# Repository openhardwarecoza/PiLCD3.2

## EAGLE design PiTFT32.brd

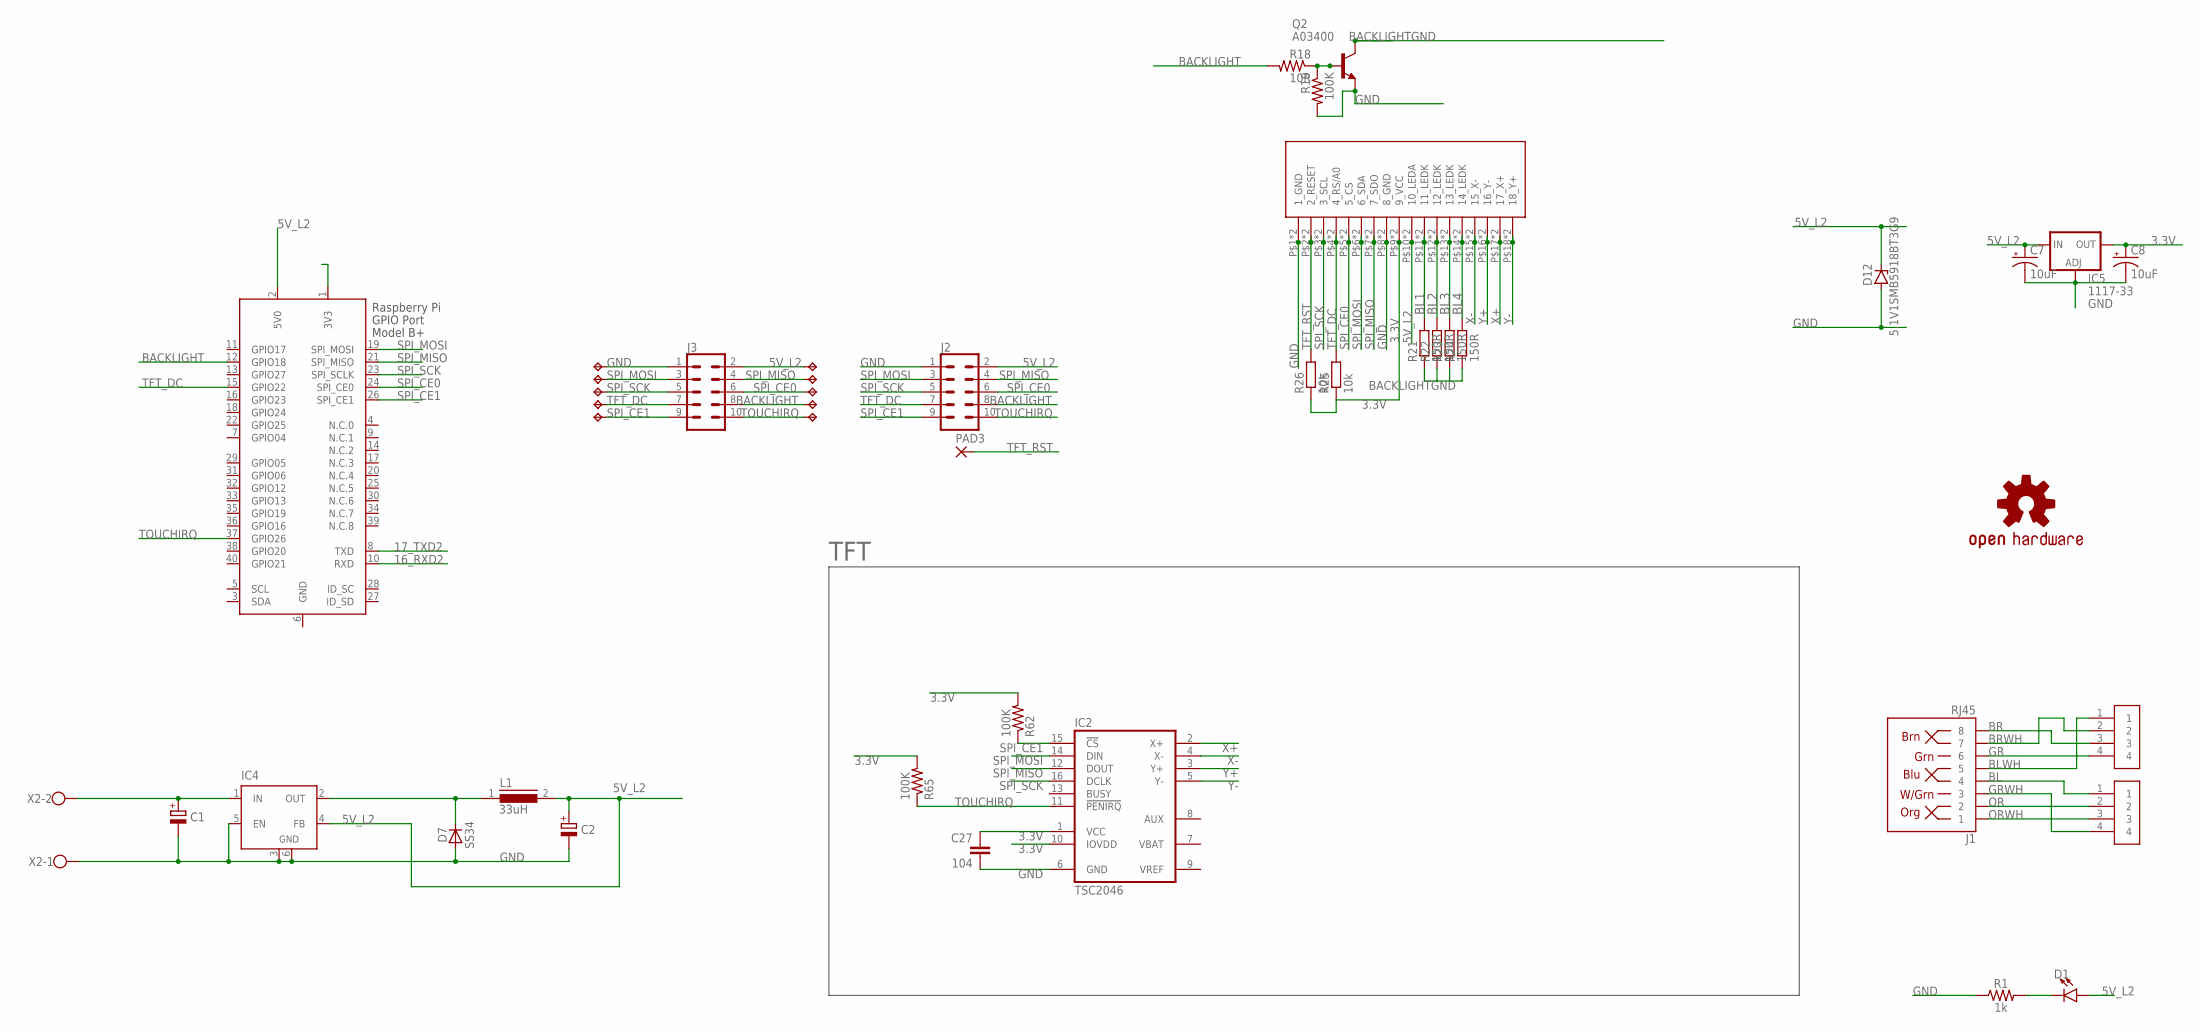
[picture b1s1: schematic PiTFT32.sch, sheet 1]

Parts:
C1, C2: CPOL-EUE3.5-8; E3,5-8
C7, C8: 10uF; EIA3216
C27: 104; C0603K
CON1, CON25: Phoenix Pluggable 3.81mm 4 way; 3.81MM-4WAY-PLUGGABLE-SCREW
D1: LED5MM; LED_5MM
D7: SS34; SOD87
D12: 5.1V1SMB5918BT3G9; SMB
IC2: TSC2046; TSSOP16
IC4: LM2596S; TO263-5
IC5: 1117-33; SOT223
J1: RJ45; RJ45-8
J2, J3: CONN_05X2SHD; 2X5-SHROUDED
L1: 33uH; DR127
LOGO1: OSHW-LOGOM; OSHW-LOGO-M
PAD3: SMD5; SMD2,54-5,08
Q2: A03400; SOT23-BEC
R1: 1k; AXIAL-0.3-KIT
R18: 10R; R0603
R19, R62, R65: 100K; R0603
R21, R22, R23, R24: 150R; R0603-ROUND
R25, R26: 10k; R0603-ROUND
TP1, TP2, TP3, TP4, TP5, TP6, TP7, TP8, TP9, TP10: TPB1,27; B1,27
U$5: TFT-DISPLAY-3.2-OB
X1: RASPI_BOARD_B+_E0; RASPI_BOARD_B+_EDGES_0DRILL
X2: W237-102

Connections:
3.3V: C8.A (+), C27.1, IC2.1 (VCC), IC2.10 (IOVDD), IC5.4 (OUT), R25.1, R26.1, R62.2, R65.2, U$5.P$9 (9_VCC), U$5.P$27 (9_VCC)
5V_L2: C2.+, C7.A (+), D1.A, D12.C, IC4.4 (FB), IC5.3 (IN), J2.2, J3.2, L1.2, TP6.TP, U$5.P$10 (10_LEDA), U$5.P$28 (10_LEDA), X1.2 (5V0)
16_RXD2: X1.10 (RXD)
17_TXD2: X1.8 (TXD)
BACKLIGHT: J2.8, J3.8, R18.2, TP9.TP, X1.12 (GPIO18)
BACKLIGHTGND: Q2.C, R21.1, R22.1, R23.1, R24.1
BL: CON1.1, J1.4
BL1: R21.2, U$5.P$11 (11_LEDK), U$5.P$29 (11_LEDK)
BL2: R22.2, U$5.P$12 (12_LEDK), U$5.P$30 (12_LEDK)
BL3: R23.2, U$5.P$13 (13_LEDK), U$5.P$31 (13_LEDK)
BL4: R24.2, U$5.P$14 (14_LEDK), U$5.P$32 (14_LEDK)
BLWH: CON25.1, J1.5
BR: CON25.3, J1.8
BRWH: CON25.2, J1.7
GND: C1.-, C2.-, C7.C (-), C8.C (-), C27.2, D7.2 (A), D12.A, IC2.6 (GND), IC4.3 (GND), IC4.5 (EN), IC4.6 (GND), IC5.1 (ADJ), J2.1, J3.1, Q2.E, R1.P$1 (1), R19.2, TP1.TP, U$5.P$1 (1_GND), U$5.P$8 (8_GND), U$5.P$19 (1_GND), U$5.P$26 (8_GND), X1.6 (GND), X2.1
GR: CON25.4, J1.6
GRWH: CON1.4, J1.3
HI-V-IN: C1.+, IC4.1 (IN), X2.2
unnamed: D1.K (C), R1.P$2 (2)
unnamed: Q2.B, R18.1, R19.1
unnamed: D7.1 (C), IC4.2 (OUT), L1.1
OR: CON1.2, J1.2
ORWH: CON1.3, J1.1
SPI_CE0: J2.6, J3.6, TP8.TP, U$5.P$5 (5_CS), U$5.P$23 (5_CS), X1.24 (SPI_CE0)
SPI_CE1: IC2.15 (!CS), J2.9, J3.9, R62.1, TP5.TP, X1.26 (SPI_CE1)
SPI_MISO: IC2.12 (DOUT), J2.4, J3.4, TP7.TP, U$5.P$7 (7_SDO), U$5.P$25 (7_SDO), X1.21 (SPI_MISO)
SPI_MOSI: IC2.14 (DIN), J2.3, J3.3, TP2.TP, U$5.P$6 (6_SDA), U$5.P$24 (6_SDA), X1.19 (SPI_MOSI)
SPI_SCK: IC2.16 (DCLK), J2.5, J3.5, TP3.TP, U$5.P$3 (3_SCL), U$5.P$21 (3_SCL), X1.23 (SPI_SCLK)
TFT_DC: J2.7, J3.7, R25.2, TP4.TP, U$5.P$4 (4_RS/A0), U$5.P$22 (4_RS/A0), X1.15 (GPIO22)
TFT_RST: PAD3.1, R26.2, U$5.P$2 (2_RESET), U$5.P$20 (2_RESET)
TOUCHIRQ: IC2.11 (!PENIRQ), J2.10, J3.10, R65.1, TP10.TP, X1.37 (GPIO26)
X+: IC2.2 (X+), U$5.P$17 (17_X+), U$5.P$35 (17_X+)
X-: IC2.4 (X-), U$5.P$15 (15_X-), U$5.P$33 (15_X-)
Y+: IC2.3 (Y+), U$5.P$16 (16_Y-), U$5.P$34 (16_Y-)
Y-: IC2.5 (Y-), U$5.P$18 (18_Y+), U$5.P$36 (18_Y+)

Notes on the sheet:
TFT

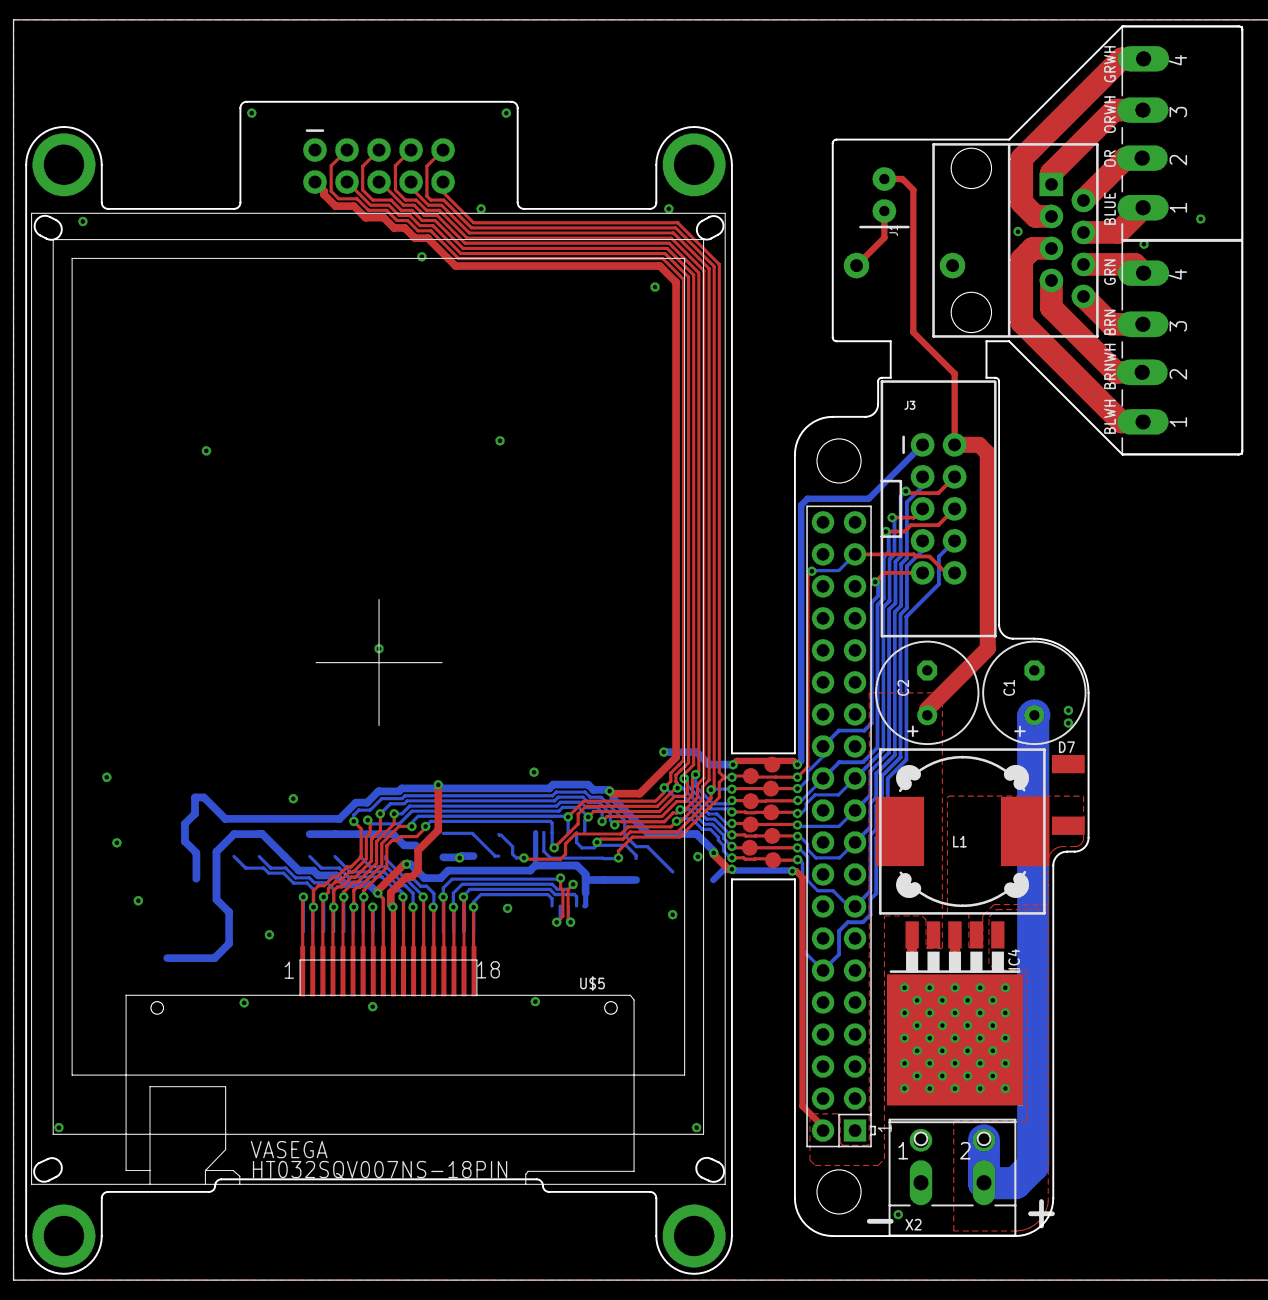
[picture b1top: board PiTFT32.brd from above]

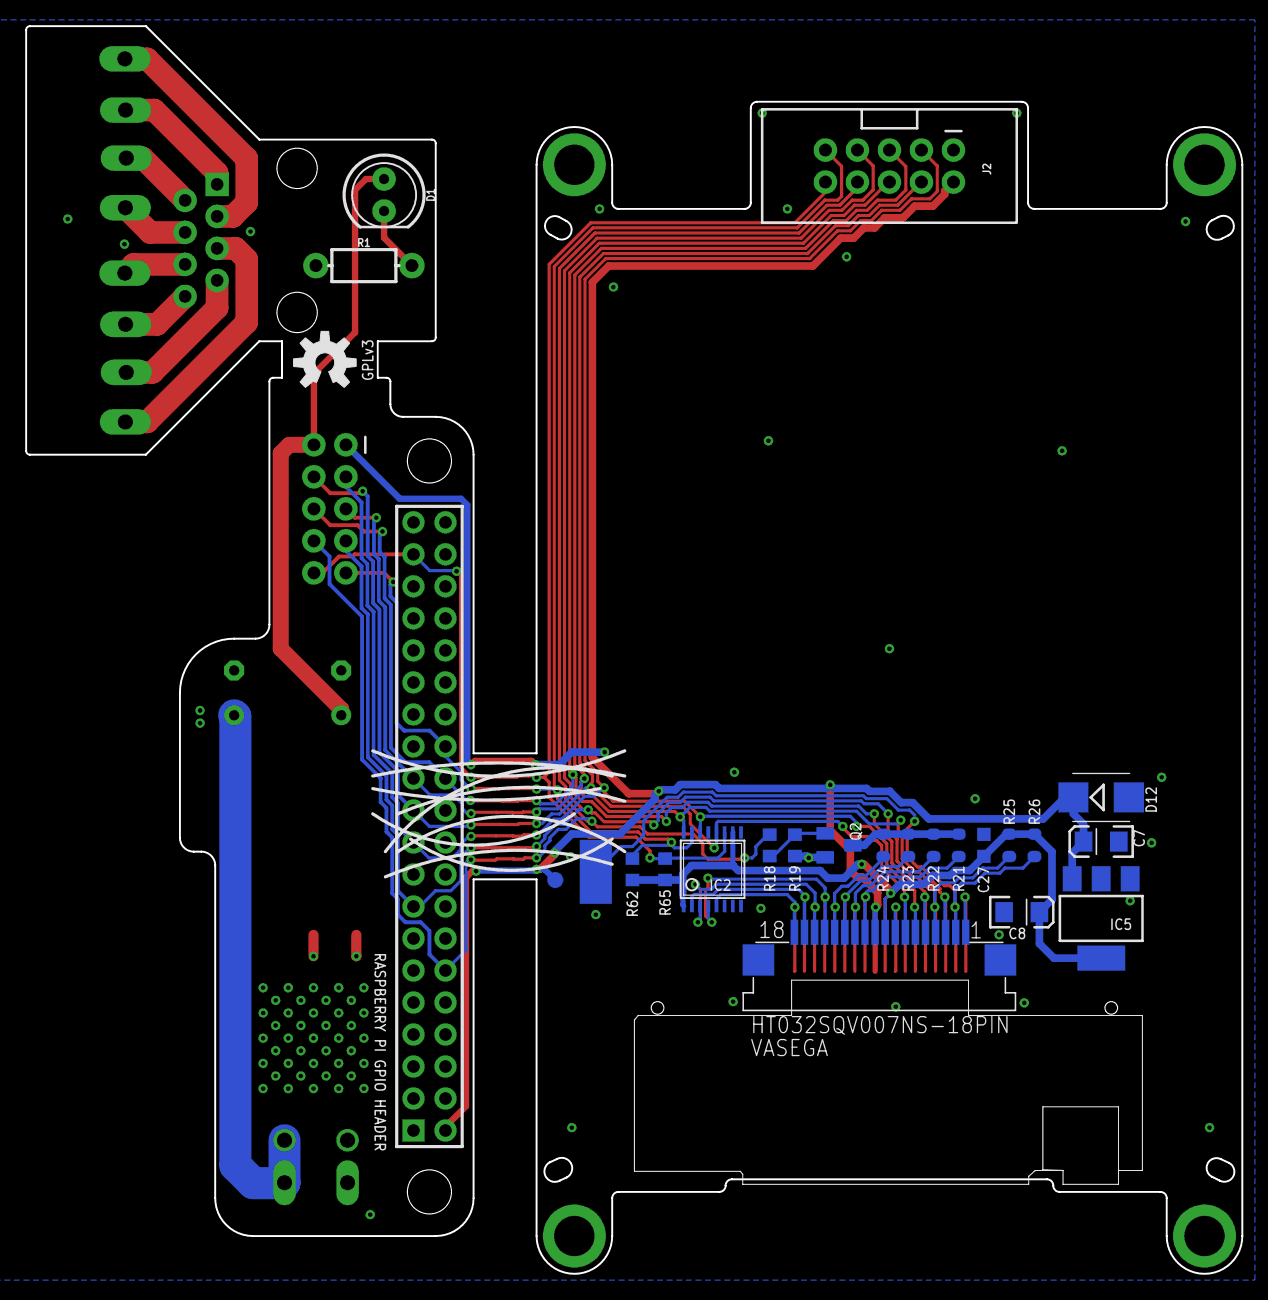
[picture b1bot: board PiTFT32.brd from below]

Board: 2 copper layers, 96.5 x 99.0 mm, 44 parts (23 on the bottom side), 33 nets.

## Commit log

2020-02-24 saving

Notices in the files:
PiTFT32.brd:
GPLv3
parts and their libraries:
SparkFun-Connectors: Licensing: Creative Commons ShareAlike 4.0 International - https://creativecommons.org/licenses/by-sa/4.0
